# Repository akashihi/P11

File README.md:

# P11 – ESPHome interface for Panasonic air conditioners and heat pumps (CN-CNT)

A small open-hardware board that connects a Panasonic air conditioner or air-to-air heat pump to
[Home Assistant](https://www.home-assistant.io/) through the indoor unit's **CN-CNT** service port.
It runs [ESPHome](https://esphome.io/) on an ESP32-C3 Super Mini with the
[`panasonic_ac`](https://github.com/DomiStyle/esphome-panasonic-ac) component. Everything stays
local: no Panasonic cloud and no Comfort Cloud adapter (CZ-TACG1).

This design is based on the
[Ingenious Makers ESPHome Panasonic Climate Interface](https://www.ingeniousmakers.com/index.php/2025/03/08/ingenious-makers-esphome-panasonic-climate-interface/).
Compared with the original, it:

- uses SMD parts throughout: AO3400A MOSFETs in place of 2N7000, US1A in place of 1N4001, 0805 resistors and an SMD electrolytic capacitor;
- adds an optional on-board **DS18B20** temperature sensor;
- is a 4-layer board with solid GND and 3.3 V inner planes.

## Features

- Full climate control from Home Assistant: mode, target temperature, fan speed and swing.
- Outdoor temperature, defrost status and live power consumption from the unit.
- Daily energy (kWh) calculated from the power reading.
- Optional room temperature from the on-board DS18B20.
- Powered from the unit's own 5 V on the CN-CNT port, so no extra power supply is needed.
- USB-C on the ESP32-C3 Super Mini for the first flash. After that, updates go over the air.

## Hardware

| | |
|---|---|
| MCU | ESP32-C3 Super Mini (4 MB flash) |
| Interface | UART, 9600 baud, 8E1, 5 V logic on the AC side |
| Level shifting | 2× AO3400A, bidirectional MOSFET shifter (3.3 V ↔ 5 V) |
| Power | 5 V from CN-CNT pin 1, 470 µF bulk capacitor, US1A reverse-polarity diode |
| PCB | 48 × 30 mm, 4 layers, 1.6 mm (F.Cu signals / In1 GND / In2 +3V3 / B.Cu) |
| EDA | KiCad 10 |

### Schematic

You can also get the schematic as a PDF: [`docs/schematic.pdf`](docs/schematic.pdf).

**Level shifter.** Each signal uses the classic single-MOSFET bidirectional shifter. The AO3400A gate
is tied to +3V3. The source goes to the ESP32 pin with a 10 kΩ pull-up to 3.3 V, and the drain goes
to the CN-CNT pin with a 10 kΩ pull-up to 5 V.

**Power.** The ESP32-C3 Super Mini is powered through its `5V` pin from CN-CNT pin 1, and its
on-board regulator supplies the 3.3 V rail. D1 sits reverse-biased across the 5 V input and
conducts if the cable is plugged in the wrong way round.

### Connections

**J1 – CN-CNT** (pin 1 is the end nearest the board edge, next to U2)

| J1 pin | CN-CNT signal | Connected to |
|---|---|---|
| 1 | +5 V | ESP32 `5V`, C1, D1 |
| 2 | TX (AC → board) | Q4 → **GPIO20** (ESP RX) |
| 3 | RX (board → AC) | Q3 → **GPIO21** (ESP TX) |
| 4 | +12 V | **not connected**; the board ignores the 12 V line |
| 5 | GND | GND |

> [!WARNING]
> CN-CNT pin 4 carries **12 V**. The board leaves it unconnected, but a cable with the wrong pin
> order can still put 12 V on the 5 V or signal lines, and that destroys the board and can damage
> the indoor unit's controller. Check your cable with a multimeter before plugging it in, and
> always switch the unit off at the breaker before you open the indoor unit.

### Cable

The CN-CNT socket on the indoor unit is a JST PA series header, 5 pins at 2.0 mm pitch, which
mates with a **JST PAP-05V-S** housing. J1 on the board is a standard 2.54 mm pin header, so the
two need an adapter cable:

- **AC end:** a JST PAP-05V-S housing with SPHD-001T-P0.5 crimp contacts.
- **Board end:** a 5-pin 2.54 mm Dupont housing.

Wire it straight through, pin 1 → pin 1 through pin 5 → pin 5. You can leave the pin 4 (12 V)
wire out, because J1 pin 4 isn't connected anyway.

## Bill of materials

| Ref | Qty | Value | Description | Package |
|---|---|---|---|---|
| U1 | 1 | ESP32-C3 Super Mini | ESP32-C3 dev board with USB-C | Module, 2× 8 pin |
| Q3, Q4 | 2 | AO3400A | N-channel MOSFET, 30 V / 5.7 A, logic level | SOT-23 |
| D1 | 1 | US1A | 50 V / 1 A fast rectifier, reverse-polarity protection | SMA (DO-214AC) |
| C1 | 1 | 470 µF | Electrolytic capacitor, ≥ 10 V | SMD 8 × 10.5 mm |
| R1–R4 | 4 | 10 kΩ | Level shifter pull-ups | 0805 |
| R5 | 1 | 4.7 kΩ | 1-Wire pull-up | 0805 |
| U2 | 1 | DS18B20 | 1-Wire temperature sensor (optional) | TO-92 |
| J1 | 1 | 1×5 header | 2.54 mm pin header | THT |

You also need the adapter cable from the CN-CNT socket to J1 (see [Cable](#cable)):
1× JST PAP-05V-S housing, 5× SPHD-001T-P0.5 crimp contacts, 1× 5-pin 2.54 mm Dupont housing with
contacts, and some wire.

Any logic-level N-MOSFET in SOT-23 with V<sub>GS(th)</sub> well below 3.3 V can replace the
AO3400A, for example BSS138 or 2N7002.

## Building

1. Order the PCB. Generate Gerbers and drill files from `P11/P11.kicad_pcb` in KiCad
   (*File → Fabrication Outputs*), and order it as a **4-layer** board.
2. Solder the SMD parts first (Q3, Q4, D1, R1–R5, C1), then J1 and U2. Watch the polarity of C1
   and D1 and the orientation of U2; the silkscreen shows the correct way round for each.
3. Flash the firmware onto the ESP32-C3 Super Mini over USB-C (see [Firmware](#firmware)) while
   it's still loose. Once the module is soldered in, C1 blocks a straight USB-C plug (see
   [Known issues](#known-issues)).
4. Solder the ESP32-C3 Super Mini to the board.

Use this top view as a placement reference. J1 pin 1 is on the left, at the board edge.

> [!CAUTION]
> Don't power the board from USB and the CN-CNT port at the same time. Many ESP32-C3 Super Mini
> clones have no diode between USB VBUS and the `5V` pin, so the two supplies would back-feed
> each other.

## Firmware

The ESPHome configuration is in [`panasonic-cn-cnt.yml`](panasonic-cn-cnt.yml). It uses the
`panasonic_ac` external component in `cnt` mode:

```yaml
uart:
  tx_pin: GPIO21
  rx_pin: GPIO20
  baud_rate: 9600
  parity: EVEN

climate:
  - platform: panasonic_ac
    type: cnt
    # ...
```

Before you flash it:

1. Copy `secrets.yaml.example` to `secrets.yaml`, in the same folder as the YAML file.
2. Fill in your Wi-Fi credentials, a fallback hotspot password and an OTA update password.
3. Generate an API encryption key with `openssl rand -base64 32` and put it in
   `api_encryption_key`.

`secrets.yaml` is listed in `.gitignore`, so it won't be committed by accident.

Then flash it:

```bash
esphome run panasonic-cn-cnt.yml
```

The first flash has to go over USB. Do it before you solder the module in, or use an angled
USB-C cable on an assembled board (see [Known issues](#known-issues)). If the board isn't detected,
hold **BOOT** while you plug in USB.
After that you can update the firmware over Wi-Fi. Home Assistant finds the device on its own
through the ESPHome integration.

## Known issues

**rev 1.0: a straight USB-C cable doesn't fit.** On the assembled board, capacitor C1 sits right
in front of the ESP32-C3 Super Mini's USB-C socket and blocks a straight USB-C plug. For the first
flash you need either:

- to flash the ESP32-C3 Super Mini **before** you solder it to the board. This is how the
  prototype was built, and it fits the assembly order above, which fits the module last; or
- an **angled (90°) USB-C cable**.

After the first flash, updates go over Wi-Fi, so this only affects the first flash and recovering
a board that won't boot. If there is a rev 2, it will fix this by moving C1 out of the way of
the connector.

## Credits

- [Ingenious Makers](https://www.ingeniousmakers.com/) for the original Panasonic climate interface
  design.
- [DomiStyle/esphome-panasonic-ac](https://github.com/DomiStyle/esphome-panasonic-ac) for the
  ESPHome component and for reverse-engineering the protocol.

## License

This project is licensed under the [GNU General Public License v3.0](LICENSE). The license covers
the hardware design files, documentation and ESPHome configuration.

## Disclaimer

This project is not affiliated with or endorsed by Panasonic. Opening your indoor unit and
connecting third-party hardware may void its warranty. You build and use this project at your own
risk.

## Authors

* **Denis Chaplygin** - *Initial work* - [akashihi](https://github.com/akashihi)

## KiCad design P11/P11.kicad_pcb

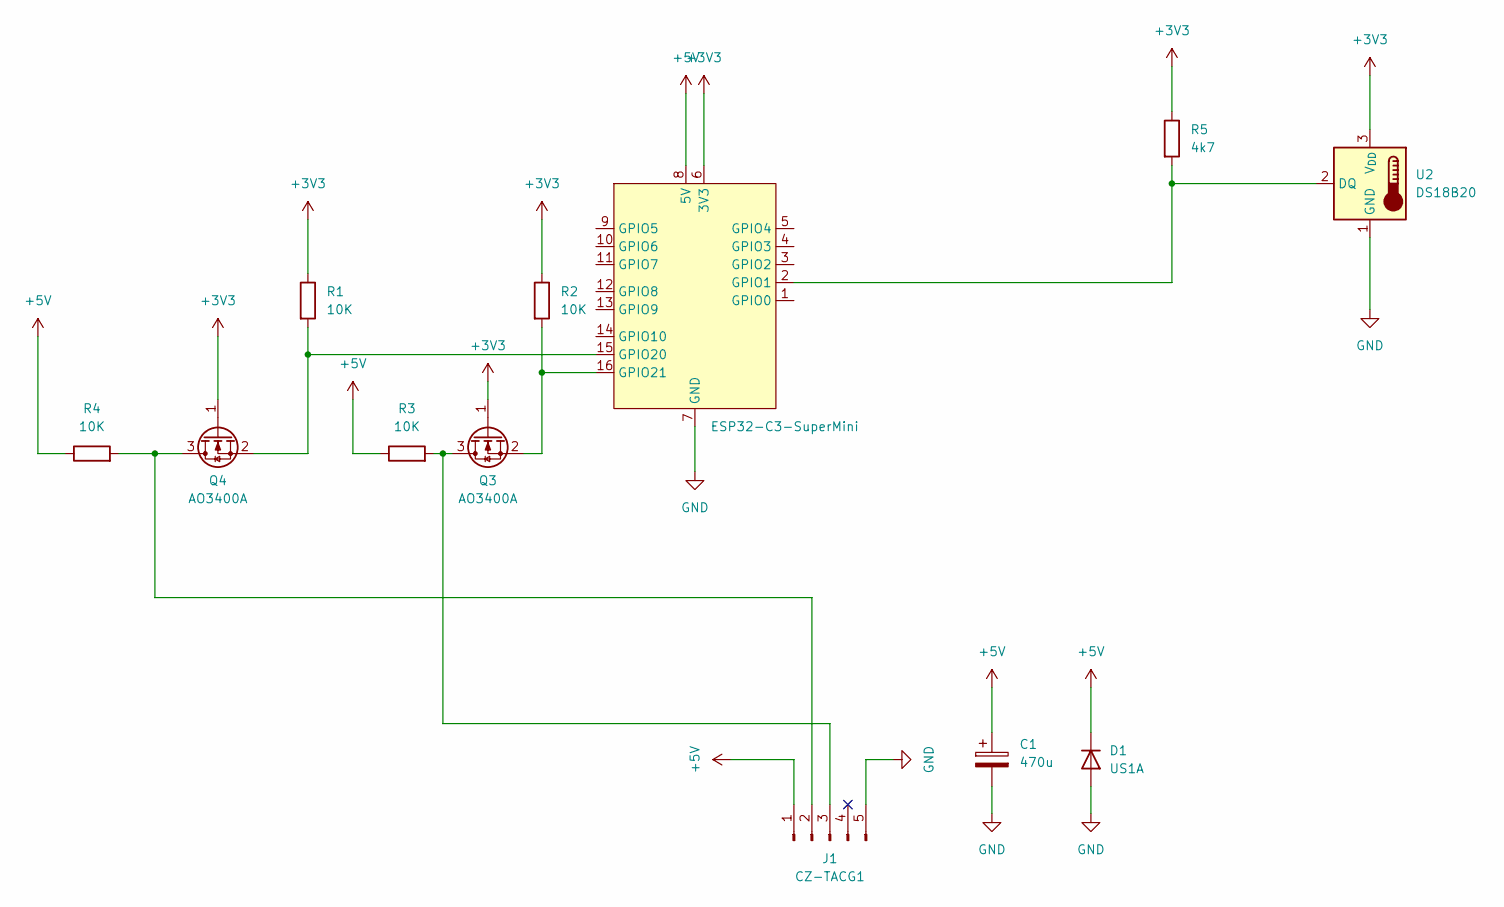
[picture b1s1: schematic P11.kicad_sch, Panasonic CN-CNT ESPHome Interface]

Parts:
C1: 470u; CP_Elec_8x10.5
D1: US1A; D_SMA
J1: CZ-TACG1; PinHeader_1x05_P2.54mm_Vertical
Q3, Q4: AO3400A; SOT-23
R1, R2, R3, R4: 10K; R_0805_2012Metric
R5: 4k7; R_0805_2012Metric
U1: ESP32-C3-SuperMini
U2: DS18B20; TO-92_Inline

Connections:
+3V3: Q3.1 (G), Q4.1 (G), R1.1, R2.1, R5.1, U1.6 (3V3), U2.3 (V_{DD})
+5V: C1.1, D1.1 (K), J1.1, R3.1, R4.1, U1.8 (5V)
GND: C1.2, D1.2 (A), J1.5, U1.7 (GND), U2.1 (GND)
unnamed: J1.2, Q4.3 (D), R4.2
unnamed: J1.3, Q3.3 (D), R3.2
unnamed: Q3.2 (S), R2.2, U1.16 (GPIO21)
unnamed: Q4.2 (S), R1.2, U1.15 (GPIO20)
unnamed: R5.2, U1.2 (GPIO1), U2.2 (DQ)

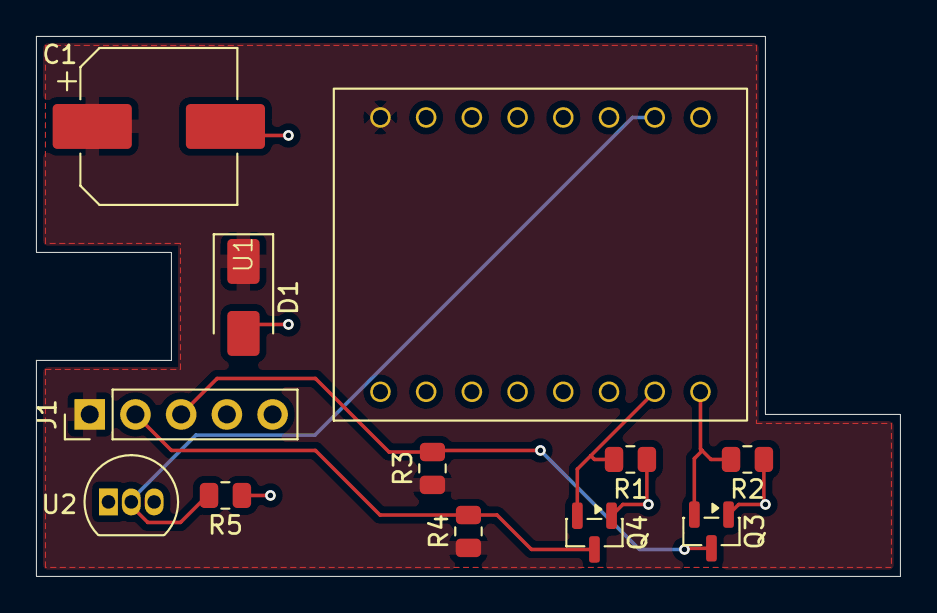
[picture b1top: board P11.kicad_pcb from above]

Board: 4 copper layers, 48.0 x 30.0 mm, 12 parts (0 on the bottom side), 8 nets.

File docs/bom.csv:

"Reference","Qty","Value","Description","Footprint","Datasheet"
"U1","1","ESP32-C3 Super Mini","ESP32-C3 development board, USB-C","ESP32-C3-SuperMini:ESP32-C3-SuperMini",""
"Q3,Q4","2","AO3400A","30V 5.7A N-channel MOSFET (level shifter)","Package_TO_SOT_SMD:SOT-23","http://www.aosmd.com/pdfs/datasheet/AO3400A.pdf"
"D1","1","US1A","50V 1A fast rectifier, reverse-polarity protection on 5V","Diode_SMD:D_SMA","https://www.diodes.com/assets/Datasheets/ds16008.pdf"
"C1","1","470uF","Polarized electrolytic capacitor, >=10V, 8x10.5 mm SMD","Capacitor_SMD:CP_Elec_8x10.5",""
"R1,R2,R3,R4","4","10k","Resistor 0805 (level shifter pull-ups)","Resistor_SMD:R_0805_2012Metric",""
"R5","1","4k7","Resistor 0805 (1-Wire pull-up)","Resistor_SMD:R_0805_2012Metric",""
"U2","1","DS18B20","1-Wire digital thermometer, TO-92 (optional)","Package_TO_SOT_THT:TO-92_Inline","http://datasheets.maximintegrated.com/en/ds/DS18B20.pdf"
"J1","1","1x05 pin header","2.54 mm pin header, 5 pins (CN-CNT cable)","Connector_PinHeader_2.54mm:PinHeader_1x05_P2.54mm_Vertical",""

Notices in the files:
P11/P11.kicad_pcb:
License: GPL-3.0
